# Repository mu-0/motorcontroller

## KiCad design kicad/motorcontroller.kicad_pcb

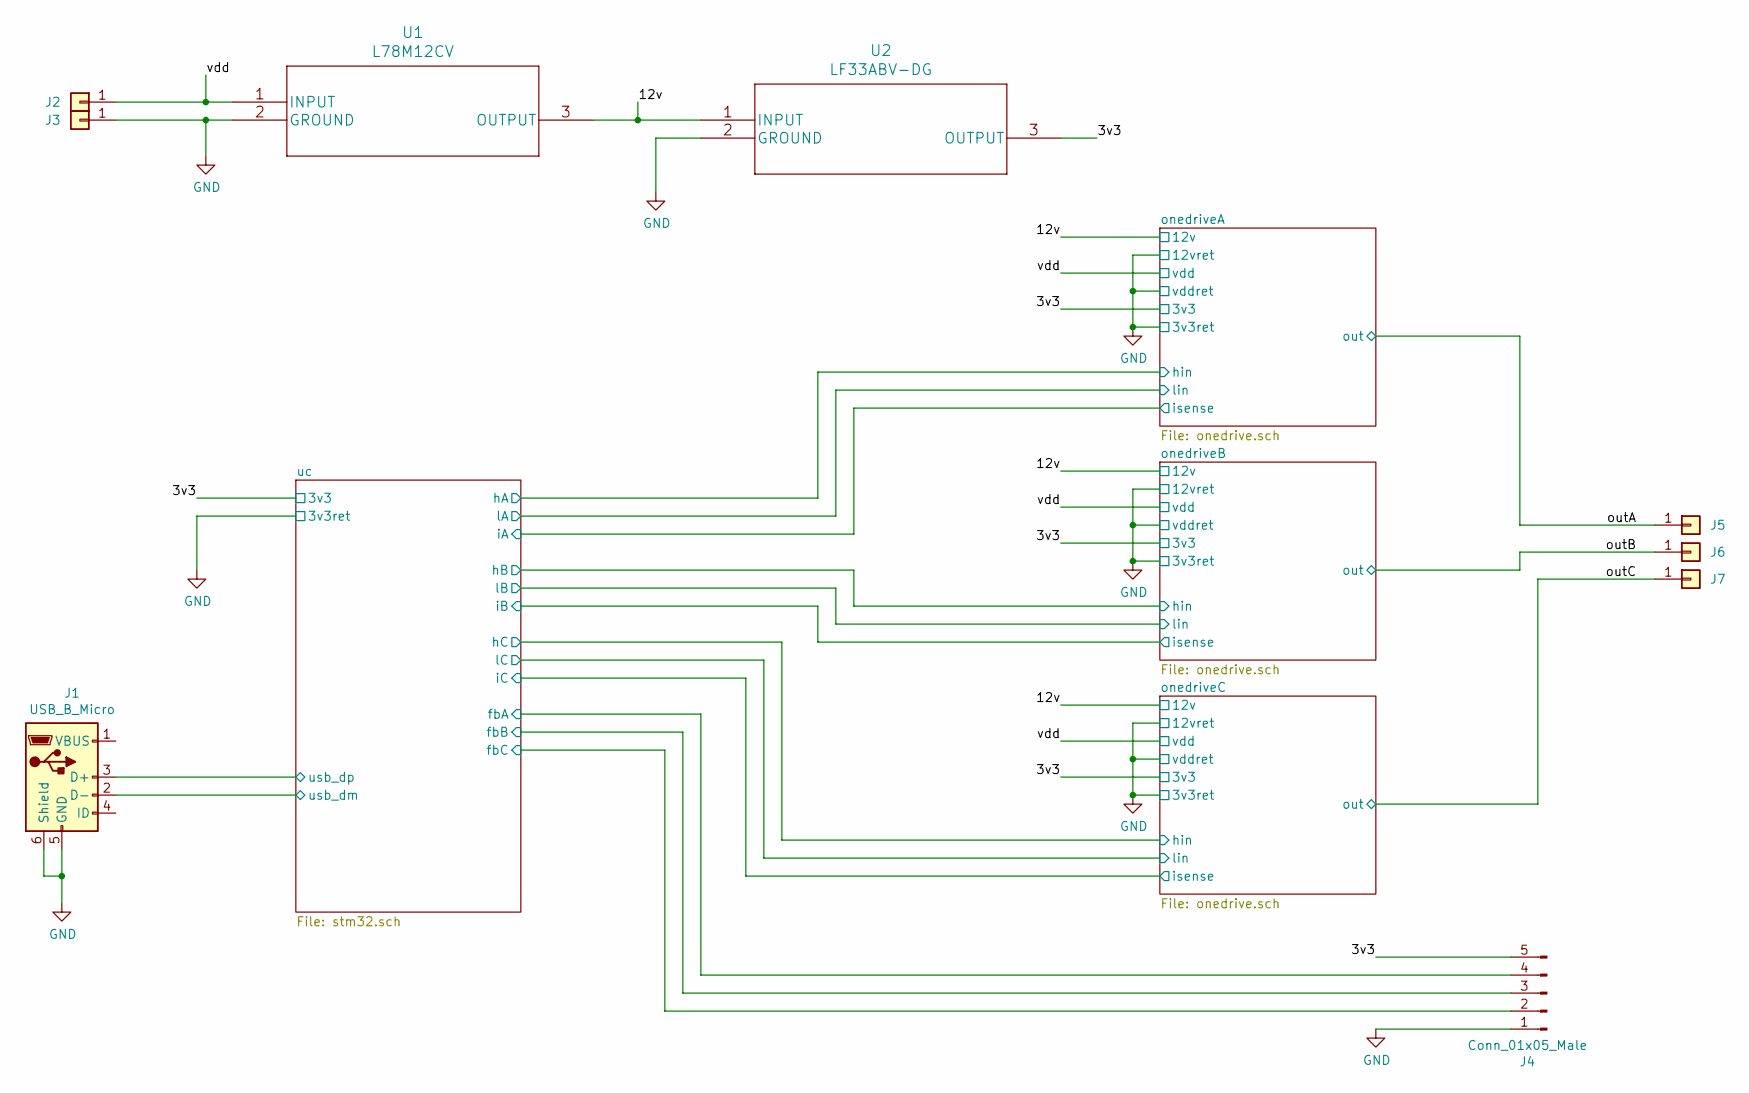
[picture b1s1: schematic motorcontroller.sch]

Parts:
J1: USB_B_Micro; USB_Micro-B_Molex-105133-0031
J2, J3, J5, J6, J7: Conn_01x01; Banana_Jack_1Pin
J4: Conn_01x05_Male; JST_PH_B5B-PH-SM4-TB_1x05-1MP_P2.00mm_Vertical
U1: L78M12CV
U2: LF33ABV-DG

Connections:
/3v3: J4.5, U2.3 (OUTPUT); also elsewhere on the board
/12v: U1.3 (OUTPUT), U2.1 (INPUT); also elsewhere on the board
/outA: J5.1; also elsewhere on the board
/outB: J6.1; also elsewhere on the board
/outC: J7.1; also elsewhere on the board
/uc/fbA: J4.4; also elsewhere on the board
/uc/fbB: J4.3; also elsewhere on the board
/uc/fbC: J4.2; also elsewhere on the board
/uc/usb_dm: J1.2 (D-); also elsewhere on the board
/uc/usb_dp: J1.3 (D+); also elsewhere on the board
/vdd: J2.1, U1.1 (INPUT); also elsewhere on the board
GND: J1.5 (GND), J1.6 (Shield), J3.1, J4.1, U1.2 (GROUND), U2.2 (GROUND); also elsewhere on the board

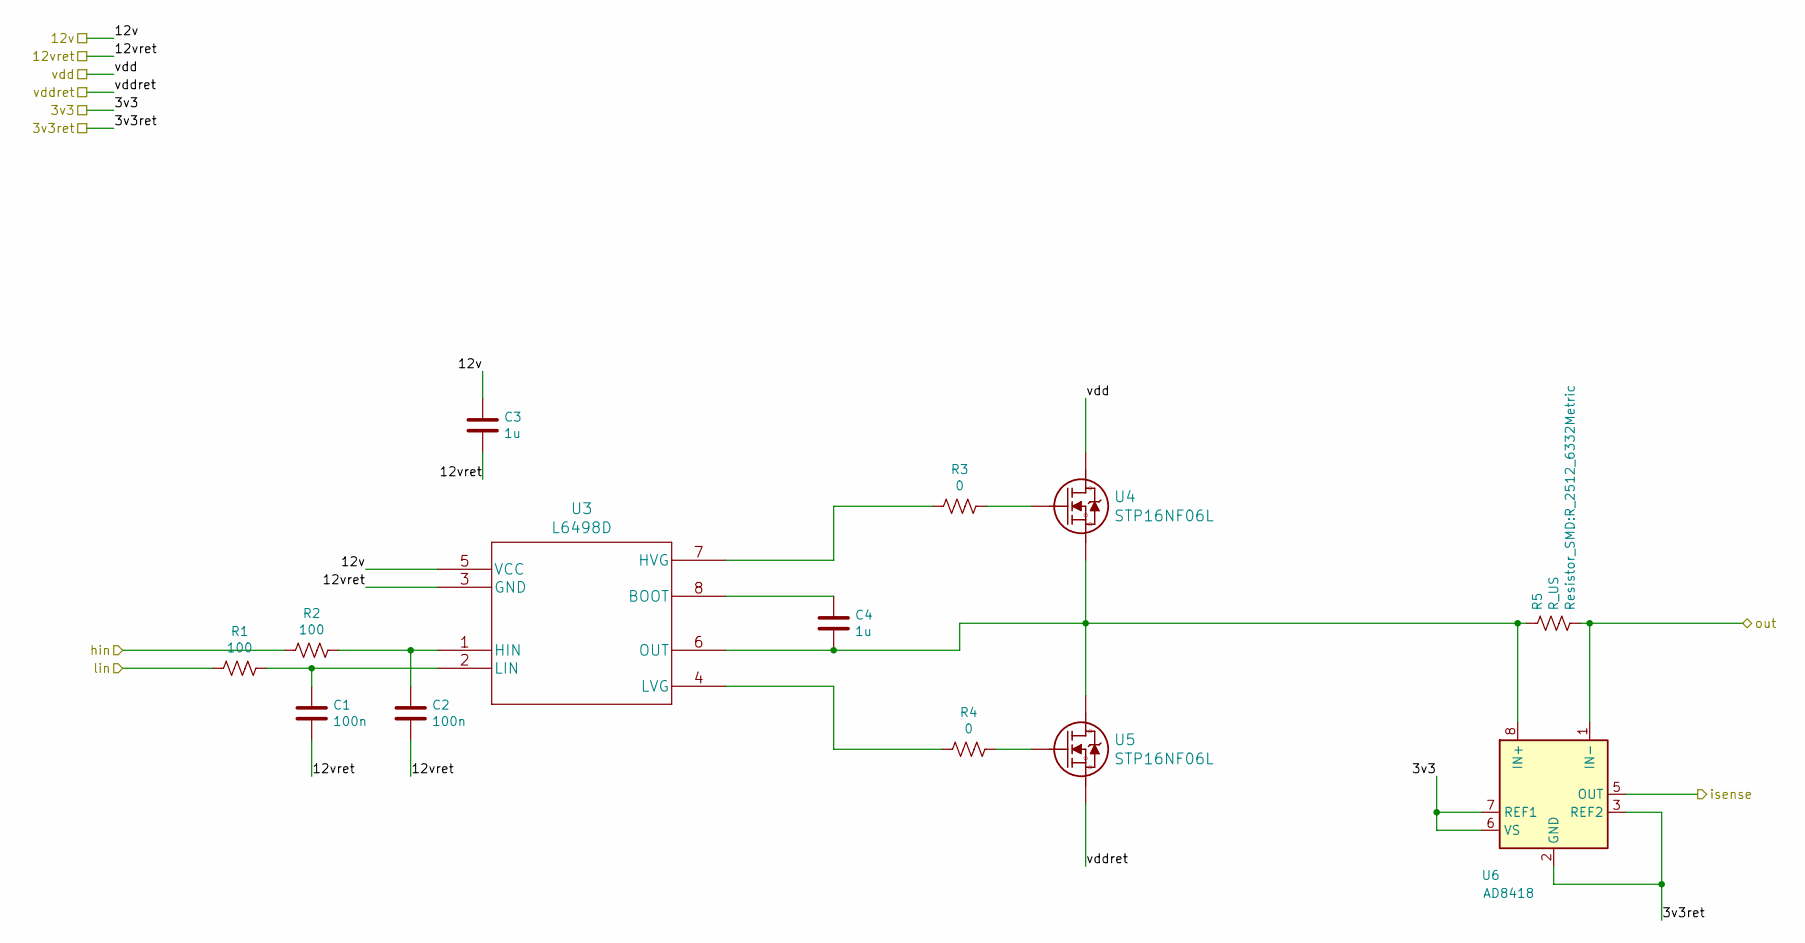
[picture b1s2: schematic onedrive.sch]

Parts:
C1, C2: 100n; C_0603_1608Metric_Pad1.05x0.95mm_HandSolder
C3, C4: 1u; C_0603_1608Metric_Pad1.05x0.95mm_HandSolder
R1, R2: 100; R_0603_1608Metric_Pad1.05x0.95mm_HandSolder
R3, R4: 0; R_0603_1608Metric_Pad1.05x0.95mm_HandSolder
R5: R_US; R_2512_6332Metric
U3: L6498D
U4, U5: STP16NF06L
U6: AD8418; MSOP-8_3x3mm_P0.65mm

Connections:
/3v3: U6.6 (VS), U6.7 (REF1); also elsewhere on the board
/12v: C3.1, U3.5 (VCC); also elsewhere on the board
/outA: R5.2, U6.1 (IN-); also elsewhere on the board
/uc/hA: R2.2; also elsewhere on the board
/uc/iA: U6.5 (OUT); also elsewhere on the board
/uc/lA: R1.1; also elsewhere on the board
/vdd: U4.2 (D); also elsewhere on the board
GND: C1.2, C2.2, C3.2, U3.3 (GND), U5.3 (S), U6.2 (GND), U6.3 (REF2); also elsewhere on the board
unnamed: C1.1, R1.2, U3.2 (LIN)
unnamed: C2.1, R2.1, U3.1 (HIN)
unnamed: C4.1, U3.8 (BOOT)
unnamed: C4.2, R5.1, U3.6 (OUT), U4.3 (S), U5.2 (D), U6.8 (IN+)
unnamed: R3.1, U4.1 (G)
unnamed: R3.2, U3.7 (HVG)
unnamed: R4.1, U5.1 (G)
unnamed: R4.2, U3.4 (LVG)

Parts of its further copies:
C12, C13, C16, C17: 100n; C_0603_1608Metric_Pad1.05x0.95mm_HandSolder
C14, C15, C18, C19: 1u; C_0603_1608Metric_Pad1.05x0.95mm_HandSolder
R6, R7, R11, R12: 100; R_0603_1608Metric_Pad1.05x0.95mm_HandSolder
R8, R9, R13, R14: 0; R_0603_1608Metric_Pad1.05x0.95mm_HandSolder
R10, R15: R_US; R_2512_6332Metric
U8, U12: L6498D
U9, U10, U13, U14: STP16NF06L
U11, U15: AD8418; MSOP-8_3x3mm_P0.65mm

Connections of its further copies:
/3v3: U11.6 (VS), U11.7 (REF1), U15.6 (VS), U15.7 (REF1); also elsewhere on the board
/12v: C14.1, C18.1, U8.5 (VCC), U12.5 (VCC); also elsewhere on the board
/outB: R10.2, U11.1 (IN-); also elsewhere on the board
/outC: R15.2, U15.1 (IN-); also elsewhere on the board
/uc/hB: R7.2; also elsewhere on the board
/uc/hC: R12.2; also elsewhere on the board
/uc/iB: U11.5 (OUT); also elsewhere on the board
/uc/iC: U15.5 (OUT); also elsewhere on the board
/uc/lB: R6.1; also elsewhere on the board
/uc/lC: R11.1; also elsewhere on the board
/vdd: U9.2 (D), U13.2 (D); also elsewhere on the board
GND: C12.2, C13.2, C14.2, C16.2, C17.2, C18.2, U8.3 (GND), U10.3 (S), U11.2 (GND), U11.3 (REF2), U12.3 (GND), U14.3 (S), U15.2 (GND), U15.3 (REF2); also elsewhere on the board
unnamed: C12.1, R6.2, U8.2 (LIN)
unnamed: C13.1, R7.1, U8.1 (HIN)
unnamed: C15.1, U8.8 (BOOT)
unnamed: C15.2, R10.1, U8.6 (OUT), U9.3 (S), U10.2 (D), U11.8 (IN+)
unnamed: C16.1, R11.2, U12.2 (LIN)
unnamed: C17.1, R12.1, U12.1 (HIN)
unnamed: C19.1, U12.8 (BOOT)
unnamed: C19.2, R15.1, U12.6 (OUT), U13.3 (S), U14.2 (D), U15.8 (IN+)
unnamed: R8.1, U9.1 (G)
unnamed: R8.2, U8.7 (HVG)
unnamed: R9.1, U10.1 (G)
unnamed: R9.2, U8.4 (LVG)
unnamed: R13.1, U13.1 (G)
unnamed: R13.2, U12.7 (HVG)
unnamed: R14.1, U14.1 (G)
unnamed: R14.2, U12.4 (LVG)

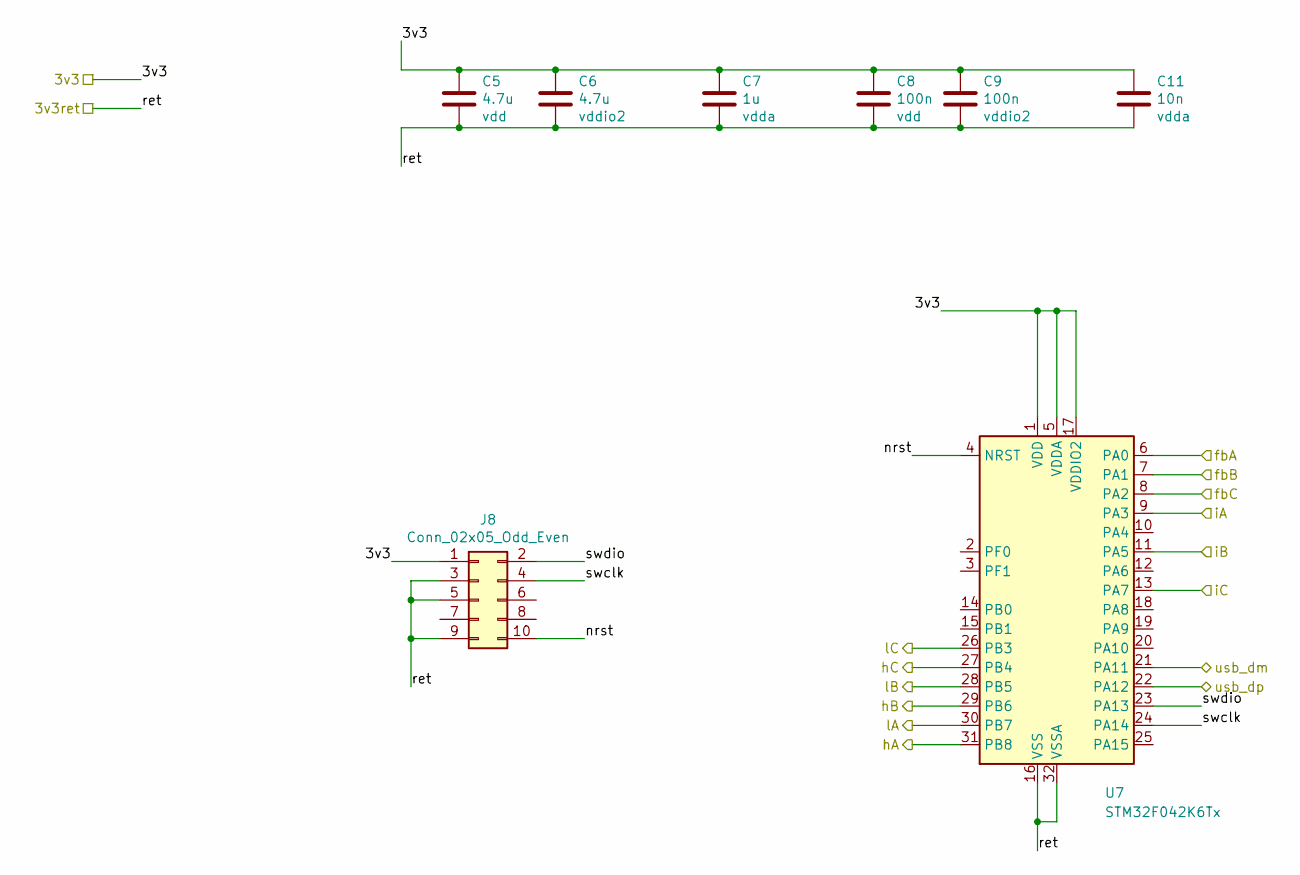
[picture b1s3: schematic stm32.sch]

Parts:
C5, C6: 4.7u; C_0603_1608Metric_Pad1.05x0.95mm_HandSolder
C7: 1u; C_0603_1608Metric_Pad1.05x0.95mm_HandSolder
C8, C9: 100n; C_0603_1608Metric_Pad1.05x0.95mm_HandSolder
C11: 10n; C_0603_1608Metric_Pad1.05x0.95mm_HandSolder
J8: Conn_02x05_Odd_Even; PinHeader_2x05_P1.27mm_Vertical_SMD
U7: STM32F042K6Tx; LQFP-32_7x7mm_P0.8mm

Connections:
/3v3: C5.1, C6.1, C7.1, C8.1, C9.1, C11.1, J8.1, U7.1 (VDD), U7.5 (VDDA), U7.17 (VDDIO2); also elsewhere on the board
/uc/fbA: U7.6 (PA0); also elsewhere on the board
/uc/fbB: U7.7 (PA1); also elsewhere on the board
/uc/fbC: U7.8 (PA2); also elsewhere on the board
/uc/hA: U7.31 (PB8); also elsewhere on the board
/uc/hB: U7.29 (PB6); also elsewhere on the board
/uc/hC: U7.27 (PB4); also elsewhere on the board
/uc/iA: U7.9 (PA3); also elsewhere on the board
/uc/iB: U7.11 (PA5); also elsewhere on the board
/uc/iC: U7.13 (PA7); also elsewhere on the board
/uc/lA: U7.30 (PB7); also elsewhere on the board
/uc/lB: U7.28 (PB5); also elsewhere on the board
/uc/lC: U7.26 (PB3); also elsewhere on the board
/uc/nrst: J8.10, U7.4 (NRST)
/uc/swclk: J8.4, U7.24 (PA14)
/uc/swdio: J8.2, U7.23 (PA13)
/uc/usb_dm: U7.21 (PA11); also elsewhere on the board
/uc/usb_dp: U7.22 (PA12); also elsewhere on the board
GND: C5.2, C6.2, C7.2, C8.2, C9.2, C11.2, J8.3, J8.5, J8.9, U7.16 (VSS), U7.32 (VSSA); also elsewhere on the board

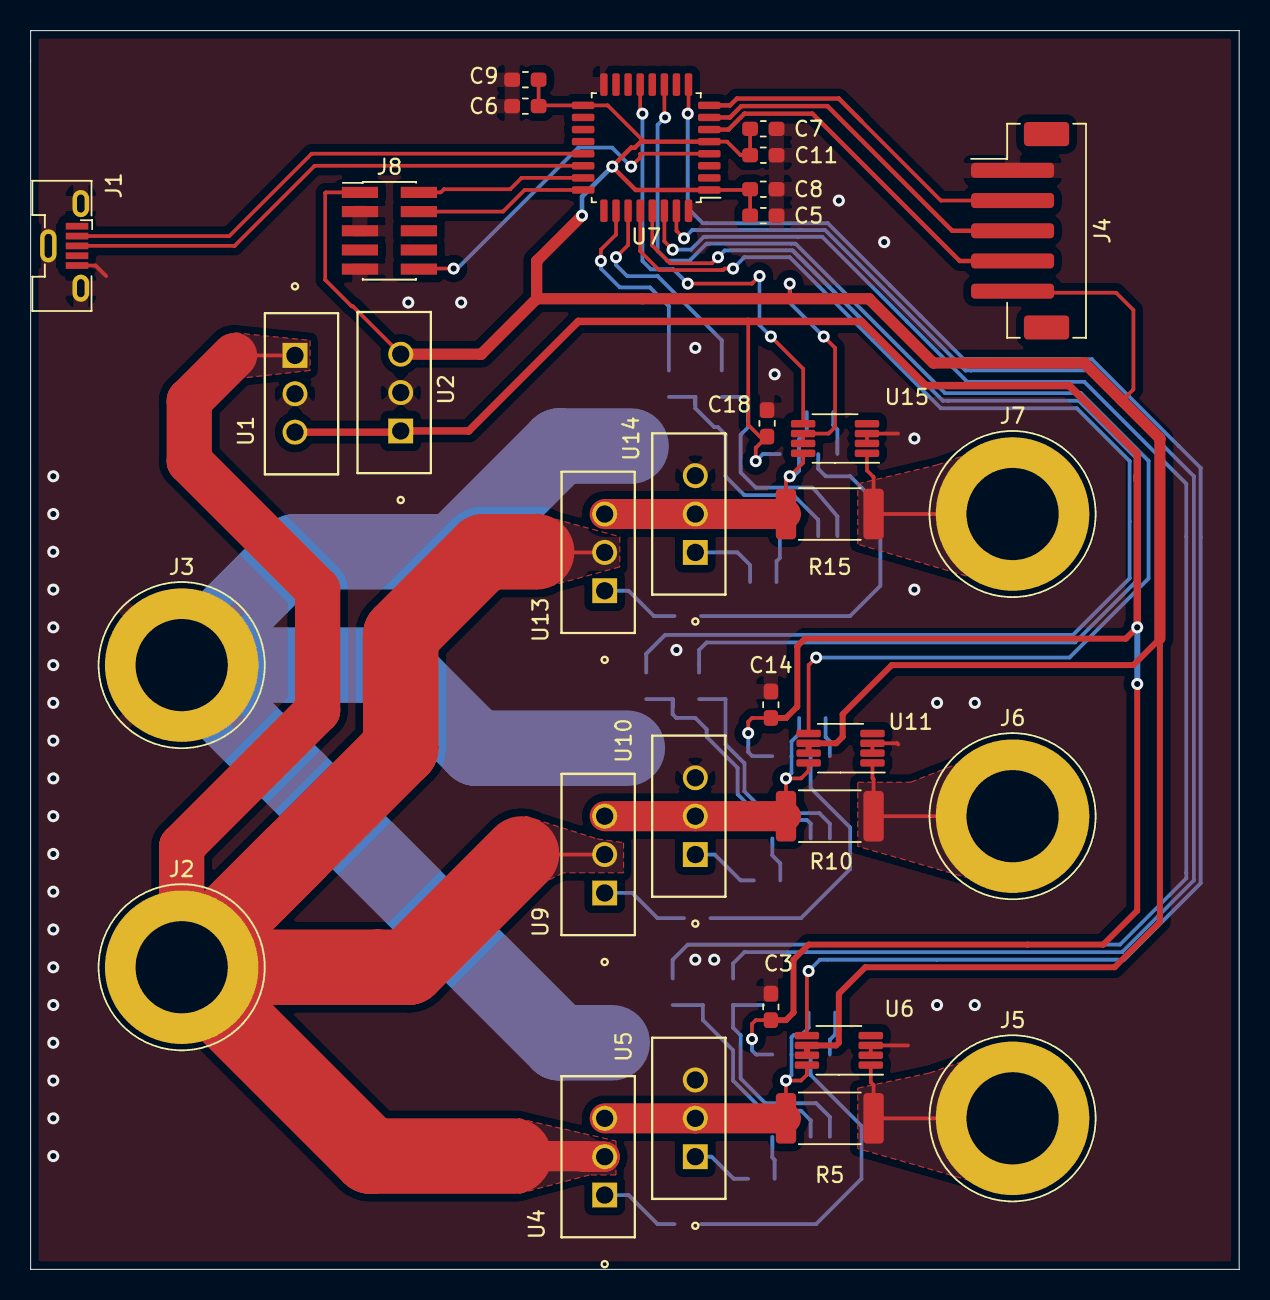
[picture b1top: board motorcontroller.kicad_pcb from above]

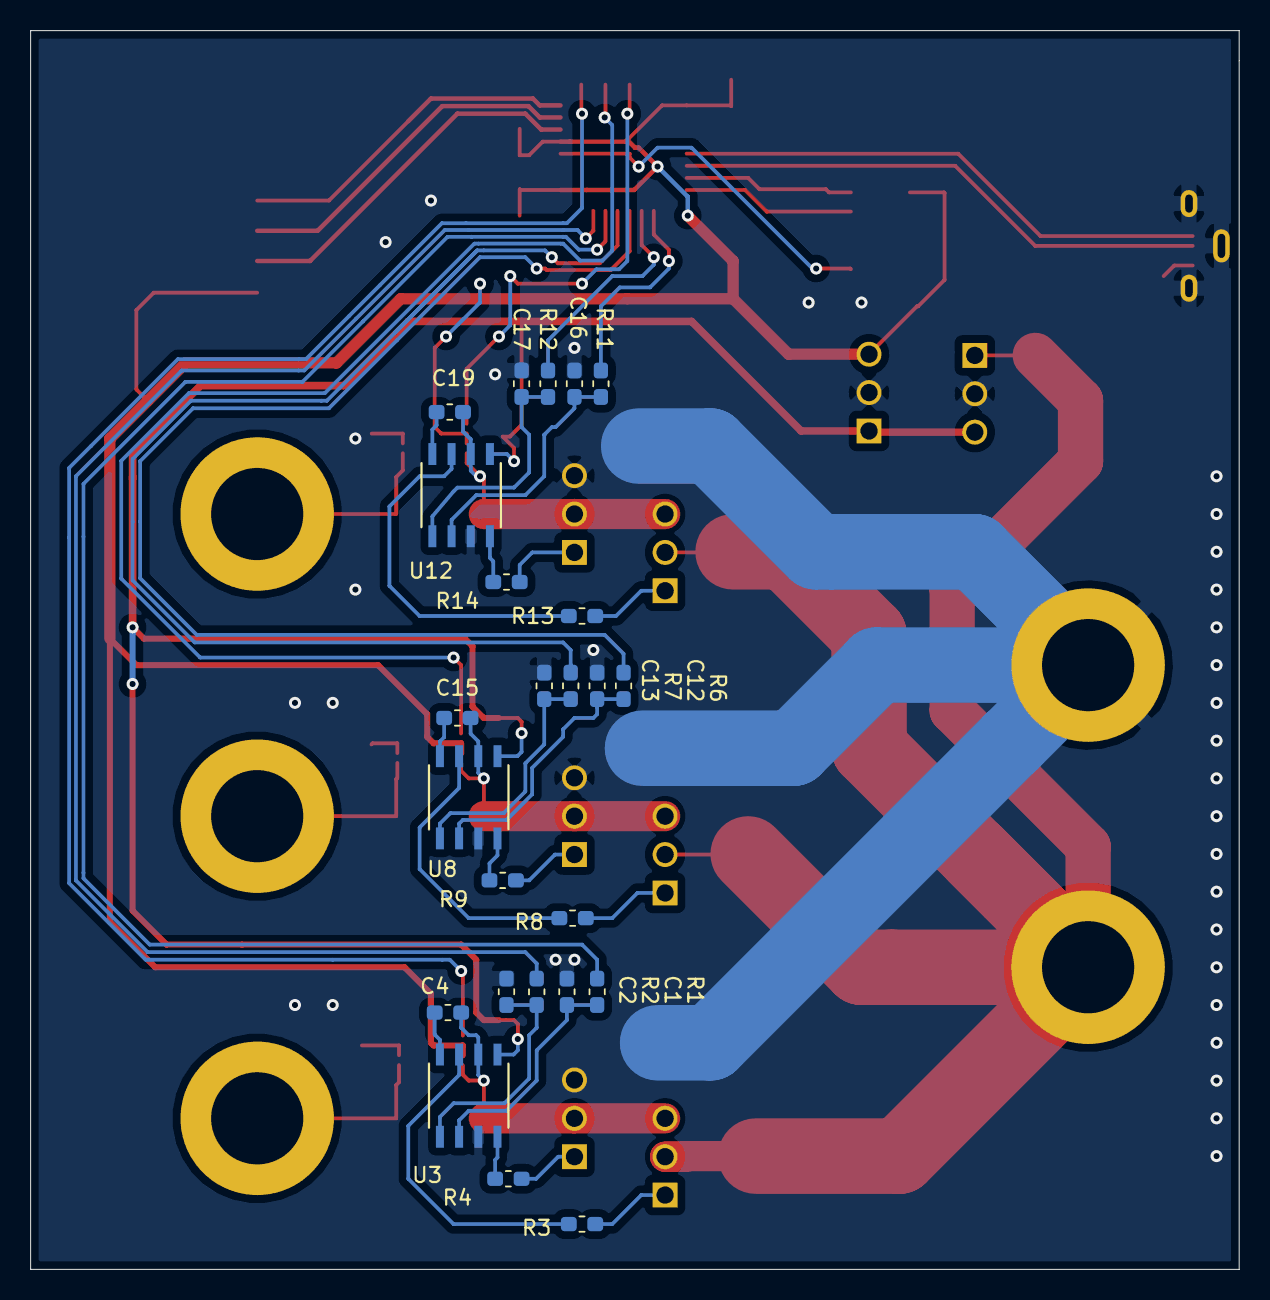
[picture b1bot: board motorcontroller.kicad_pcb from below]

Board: 2 copper layers, 80.0 x 82.0 mm, 56 parts (24 on the bottom side), 48 nets.

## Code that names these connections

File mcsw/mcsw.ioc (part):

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Mcu.Name=STM32F042K(4-6)Tx
Mcu.Package=LQFP32
Mcu.UserName=STM32F042K6Tx
PA11.Mode=Device
PA11.Signal=USB_DM
PA12.Mode=Device
PA12.Signal=USB_DP
PA13.Mode=Serial_Wire
PA13.Signal=SYS_SWDIO
PA14.Mode=Serial_Wire
PA14.Signal=SYS_SWCLK
RCC.SYSCLKFreq_VALUE=48000000
RCC.SYSCLKSource=RCC_SYSCLKSOURCE_HSI48
board=custom

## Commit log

2020-12-27 release20201227

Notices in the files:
parts and their libraries:
Copyright 2016 Accelerated Designs. All rights reserved.
